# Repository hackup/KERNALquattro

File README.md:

# KERNALquattro

The KERNALquattro is a compact, versatile, and still relatively cheap replacement for 2364 ROMs as found in the Commodore 64 and other 8-bit computers of that time. It provides 32KB of memory using an AT28HC256 EEPROM, thus holding the equivalent of up to four 2364 ROMs. Those four banks can be selected using a DIP switch, solder bridges, or by external means using the connector.

An adapter board is provided which maps the pins of the KERNALquattro back to a 28C256 DIP EEPROM. This allows the EEPROM to be programmed using a standard programmer like the TL866.

See my [blog post](https://www.hackup.net/2022/05/the-kernal-quattro-a-2364-rom-replacement/) for more details.

 **USE AT YOUR OWN RISK!**.

## License
[
](http://creativecommons.org/licenses/by-nc-sa/4.0/)

This work is licensed under a
[Creative Commons Attribution-NonCommercial-ShareAlike 4.0 International License](http://creativecommons.org/licenses/by-nc-sa/4.0/).

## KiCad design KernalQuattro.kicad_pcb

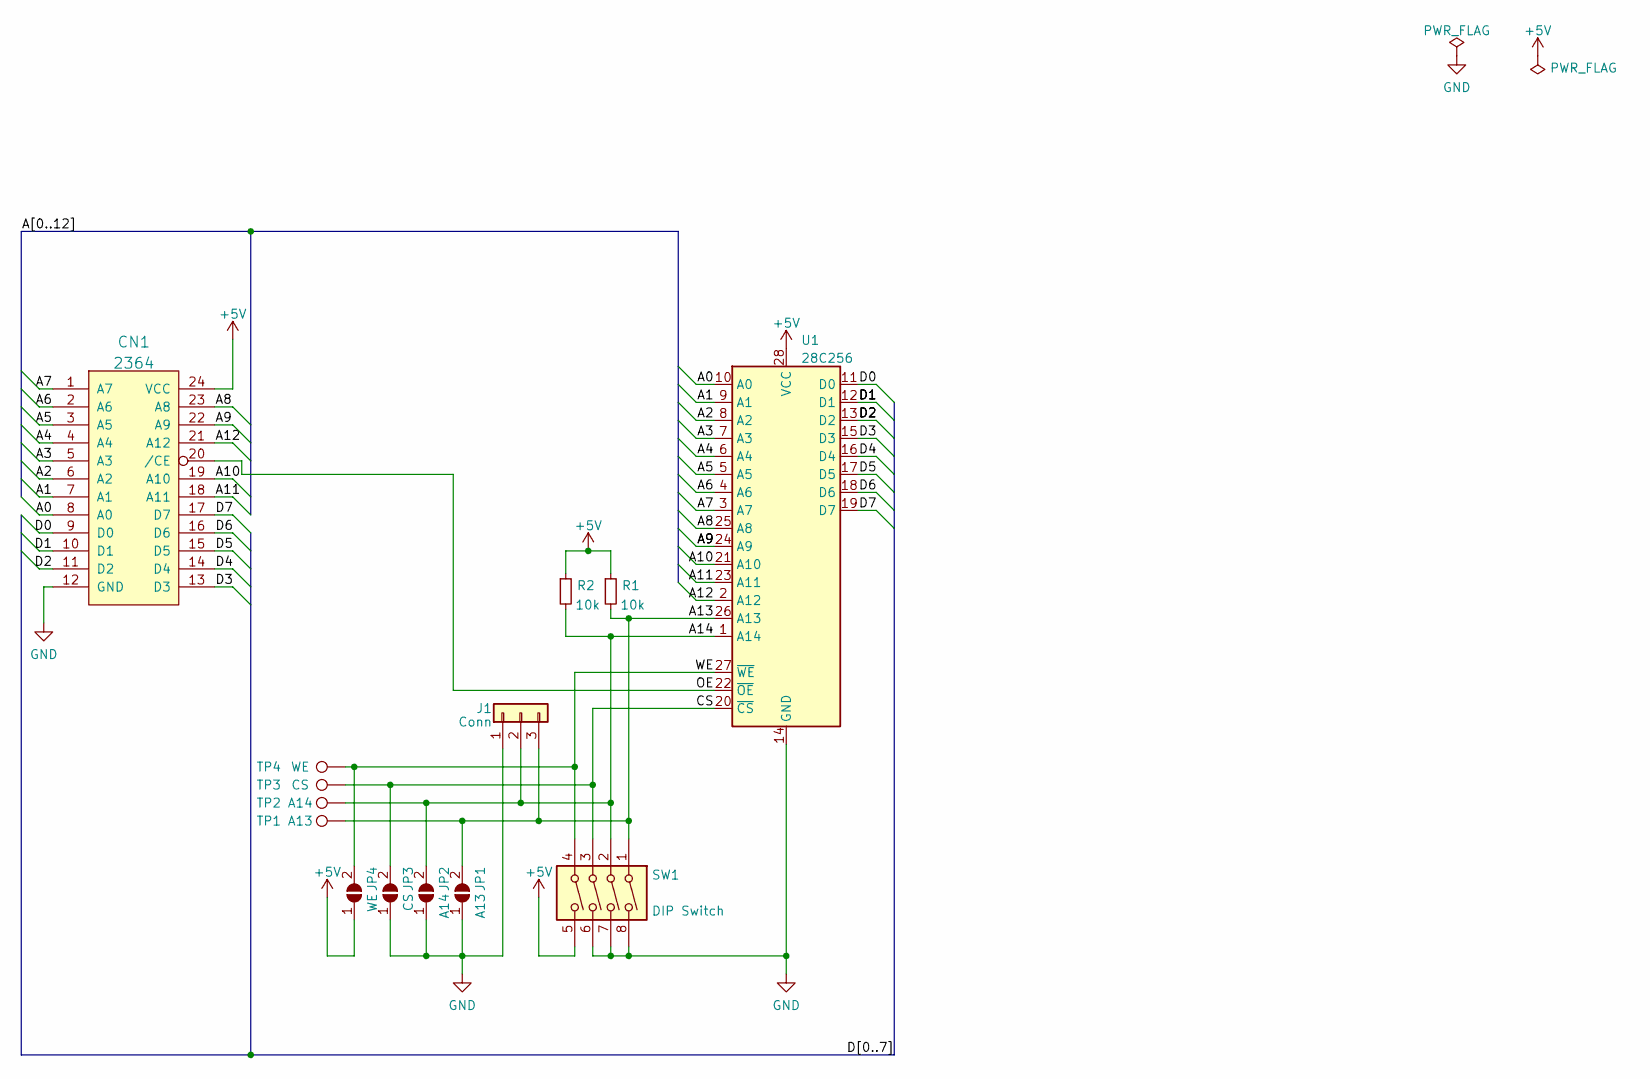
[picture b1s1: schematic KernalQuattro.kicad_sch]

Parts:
CN1: 2364; DIP-24_W15.24mm_Socket
J1: Conn; PinHeader_1x03_P2.54mm_Horizontal
JP1: A13; SolderJumper-2_slim
JP2: A14; SolderJumper-2_slim
JP3: CS; SolderJumper-2_slim
JP4: WE; SolderJumper-2_slim
R1, R2: 10k; R_0805_2012Metric
SW1: DIP Switch; SW_DIP_SPSTx04_Slide_6.7x11.72mm_W8.61mm_P2.54mm_LowProfile
TP1: A13; TestPoint_Pad_D1.5mm
TP2: A14; TestPoint_Pad_D1.5mm
TP3: CS; TestPoint_Pad_D1.5mm
TP4: WE; TestPoint_Pad_D1.5mm
U1: 28C256; SOIC-28W_7.5x17.9mm_P1.27mm

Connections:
+5V: CN1.24 (VCC), JP4.1 (A), R1.1, R2.1, SW1.5, U1.28 (VCC)
/A0: CN1.8 (A0), U1.10 (A0)
/A1: CN1.7 (A1), U1.9 (A1)
/A2: CN1.6 (A2), U1.8 (A2)
/A3: CN1.5 (A3), U1.7 (A3)
/A4: CN1.4 (A4), U1.6 (A4)
/A5: CN1.3 (A5), U1.5 (A5)
/A6: CN1.2 (A6), U1.4 (A6)
/A7: CN1.1 (A7), U1.3 (A7)
/A8: CN1.23 (A8), U1.25 (A8)
/A9: CN1.22 (A9), U1.24 (A9)
/A10: CN1.19 (A10), U1.21 (A10)
/A11: CN1.18 (A11), U1.23 (A11)
/A12: CN1.21 (A12), U1.2 (A12)
/A13: J1.3, JP1.2 (B), R1.2, SW1.1, TP1.1, U1.26 (A13)
/A14: J1.2, JP2.2 (B), R2.2, SW1.2, TP2.1, U1.1 (A14)
/CS: JP3.2 (B), SW1.3, TP3.1, U1.20 (~CS)
/D0: CN1.9 (D0), U1.11 (D0)
/D1: CN1.10 (D1), U1.12 (D1)
/D2: CN1.11 (D2), U1.13 (D2)
/D3: CN1.13 (D3), U1.15 (D3)
/D4: CN1.14 (D4), U1.16 (D4)
/D5: CN1.15 (D5), U1.17 (D5)
/D6: CN1.16 (D6), U1.18 (D6)
/D7: CN1.17 (D7), U1.19 (D7)
/OE: CN1.20 (/CE), U1.22 (~OE)
/WE: JP4.2 (B), SW1.4, TP4.1, U1.27 (~WE)
GND: CN1.12 (GND), J1.1, JP1.1 (A), JP2.1 (A), JP3.1 (A), SW1.6, SW1.7, SW1.8, U1.14 (GND)

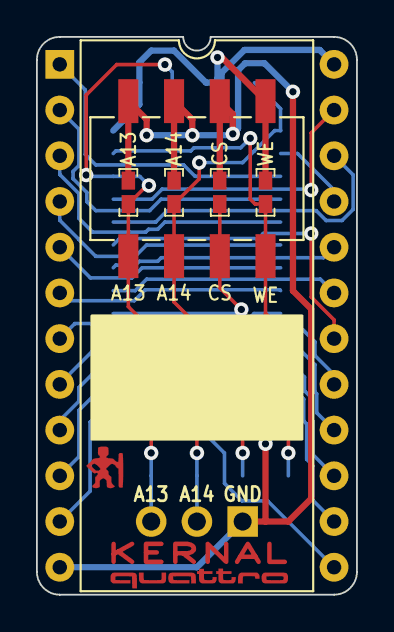
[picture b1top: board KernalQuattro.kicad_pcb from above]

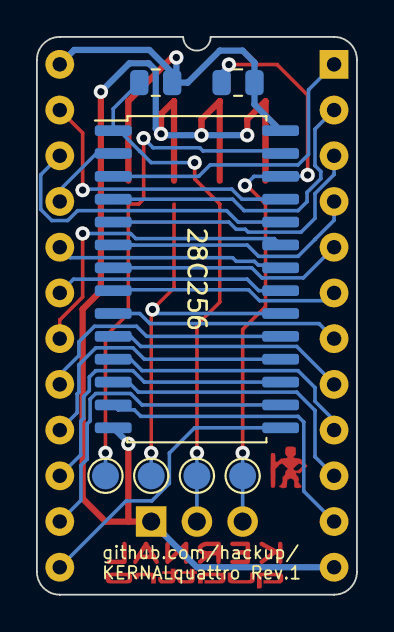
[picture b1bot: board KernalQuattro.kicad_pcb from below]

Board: 2 copper layers, 17.8 x 31.0 mm, 14 parts (7 on the bottom side), 28 nets.

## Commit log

2022-04-06 Initial import, work in progress.
2022-04-07 Work in progress.
2022-04-09 Renamed project.
2022-04-09 Rounded corners.
2022-04-09 Added programming adapter.
2022-04-11 Added custom pin header model.
2022-04-20 Generate Gerber files.
2022-05-02 Added license information.
2022-05-02 Prepare README.
2022-05-05 Fixed README.
2022-05-30 Added schematics export to repo.
